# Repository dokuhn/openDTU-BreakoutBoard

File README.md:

# openDTU Breakout Board

 [![CC BY-NC-SA 4.0][cc-by-nc-sa-shield]][cc-by-nc-sa]

To read Hoymiles inverters there is a nice project called [OpenDTU](https://github.com/tbnobody/OpenDTU) which uses an ESP32 to talk to them. 

<br>

To extend this project with a hardware component this small KiCAD board was created. With it it should be possible for the not experienced in soldering person to build an own OpenDTU easier. But also the possibility to add further ideas, like temperature sensors, display etc.. In a second step it is also possible to design a board with all the necessary components on it directly. 

<br>

The first batch of 10 pieces is partially built and tested. Further tests will follow. Extensions of the board will be maintained in a second branch. 

## Donations

As you can see I am in the process of developing a SMT/SMD variant. To support the first 10-25 prototype boards you are welcome to make a donation. This donation should be used to compensate the material costs for components, boards and consumables (soldering paste, etc.). Through my membership in the [Linux User Group Saar e.V.](https://lugsaar.de/) you support more than just me, you also support our community in similar creative and technical projects in the open source and open hardware domain. 

-PayPal: 

## Renderings

## Development

As described in the previous section, extensions or development stages are maintained in a separate branch. This section is to show exemplarily where the current developments are. Currently a SMD/SMT variant of the board is designed (see picture with the first placement). The SMT will make the board much smaller of course, so it will fit into small cases. All needed components for operation will be on the board. 

### New Features:

- All components on just one board
- Stable voltage supply
- MicroSD slot with support for a small file system to store e.g. measurement series (CSV or JSON files)
- USB-C (now more common than microUSB)
- Option to connect a small (I2C) display

##  Hardware you need

### ESP32 board

In principle, the hardware recommended [here](https://github.com/tbnobody/OpenDTU) has been used in this project. Unfortunately there are many different variants, especially in the MCU boards, so that you must be very careful that your board is pin-compatible with the following figure. 

[figure source](https://i0.wp.com/www.teachmemicro.com/wp-content/uploads/2020/06/NodeMCU-32S-Pinout.jpg?ssl=1)

### Capacitor

As you can see in the graphics above, an electrolytic capacitor is placed between the two boards. This capacitor should be as close as possible to the NRF24L01+ radio board. The size of the capacity should not be larger than 100 uF, typically capacity like 10uF or 22uF are recommended. This also corresponds to the typical capacity in the AP1117 datasheets (keep in mind that the noboard capacity of the ESP32 board has to be added). The voltage stability has to be higher than 3.3V, so all common 5V, 6.3V, 6.5V, 10V, 25V or even 50V are more than enough. 

## Case

## License 

This work is licensed under a
[Creative Commons Attribution-NonCommercial-ShareAlike 4.0 International License][cc-by-nc-sa].

[![CC BY-NC-SA 4.0][cc-by-nc-sa-image]][cc-by-nc-sa]

[cc-by-nc-sa]: http://creativecommons.org/licenses/by-nc-sa/4.0/
[cc-by-nc-sa-image]: https://licensebuttons.net/l/by-nc-sa/4.0/88x31.png
[cc-by-nc-sa-shield]: https://img.shields.io/badge/License-CC%20BY--NC--SA%204.0-lightgrey.svg

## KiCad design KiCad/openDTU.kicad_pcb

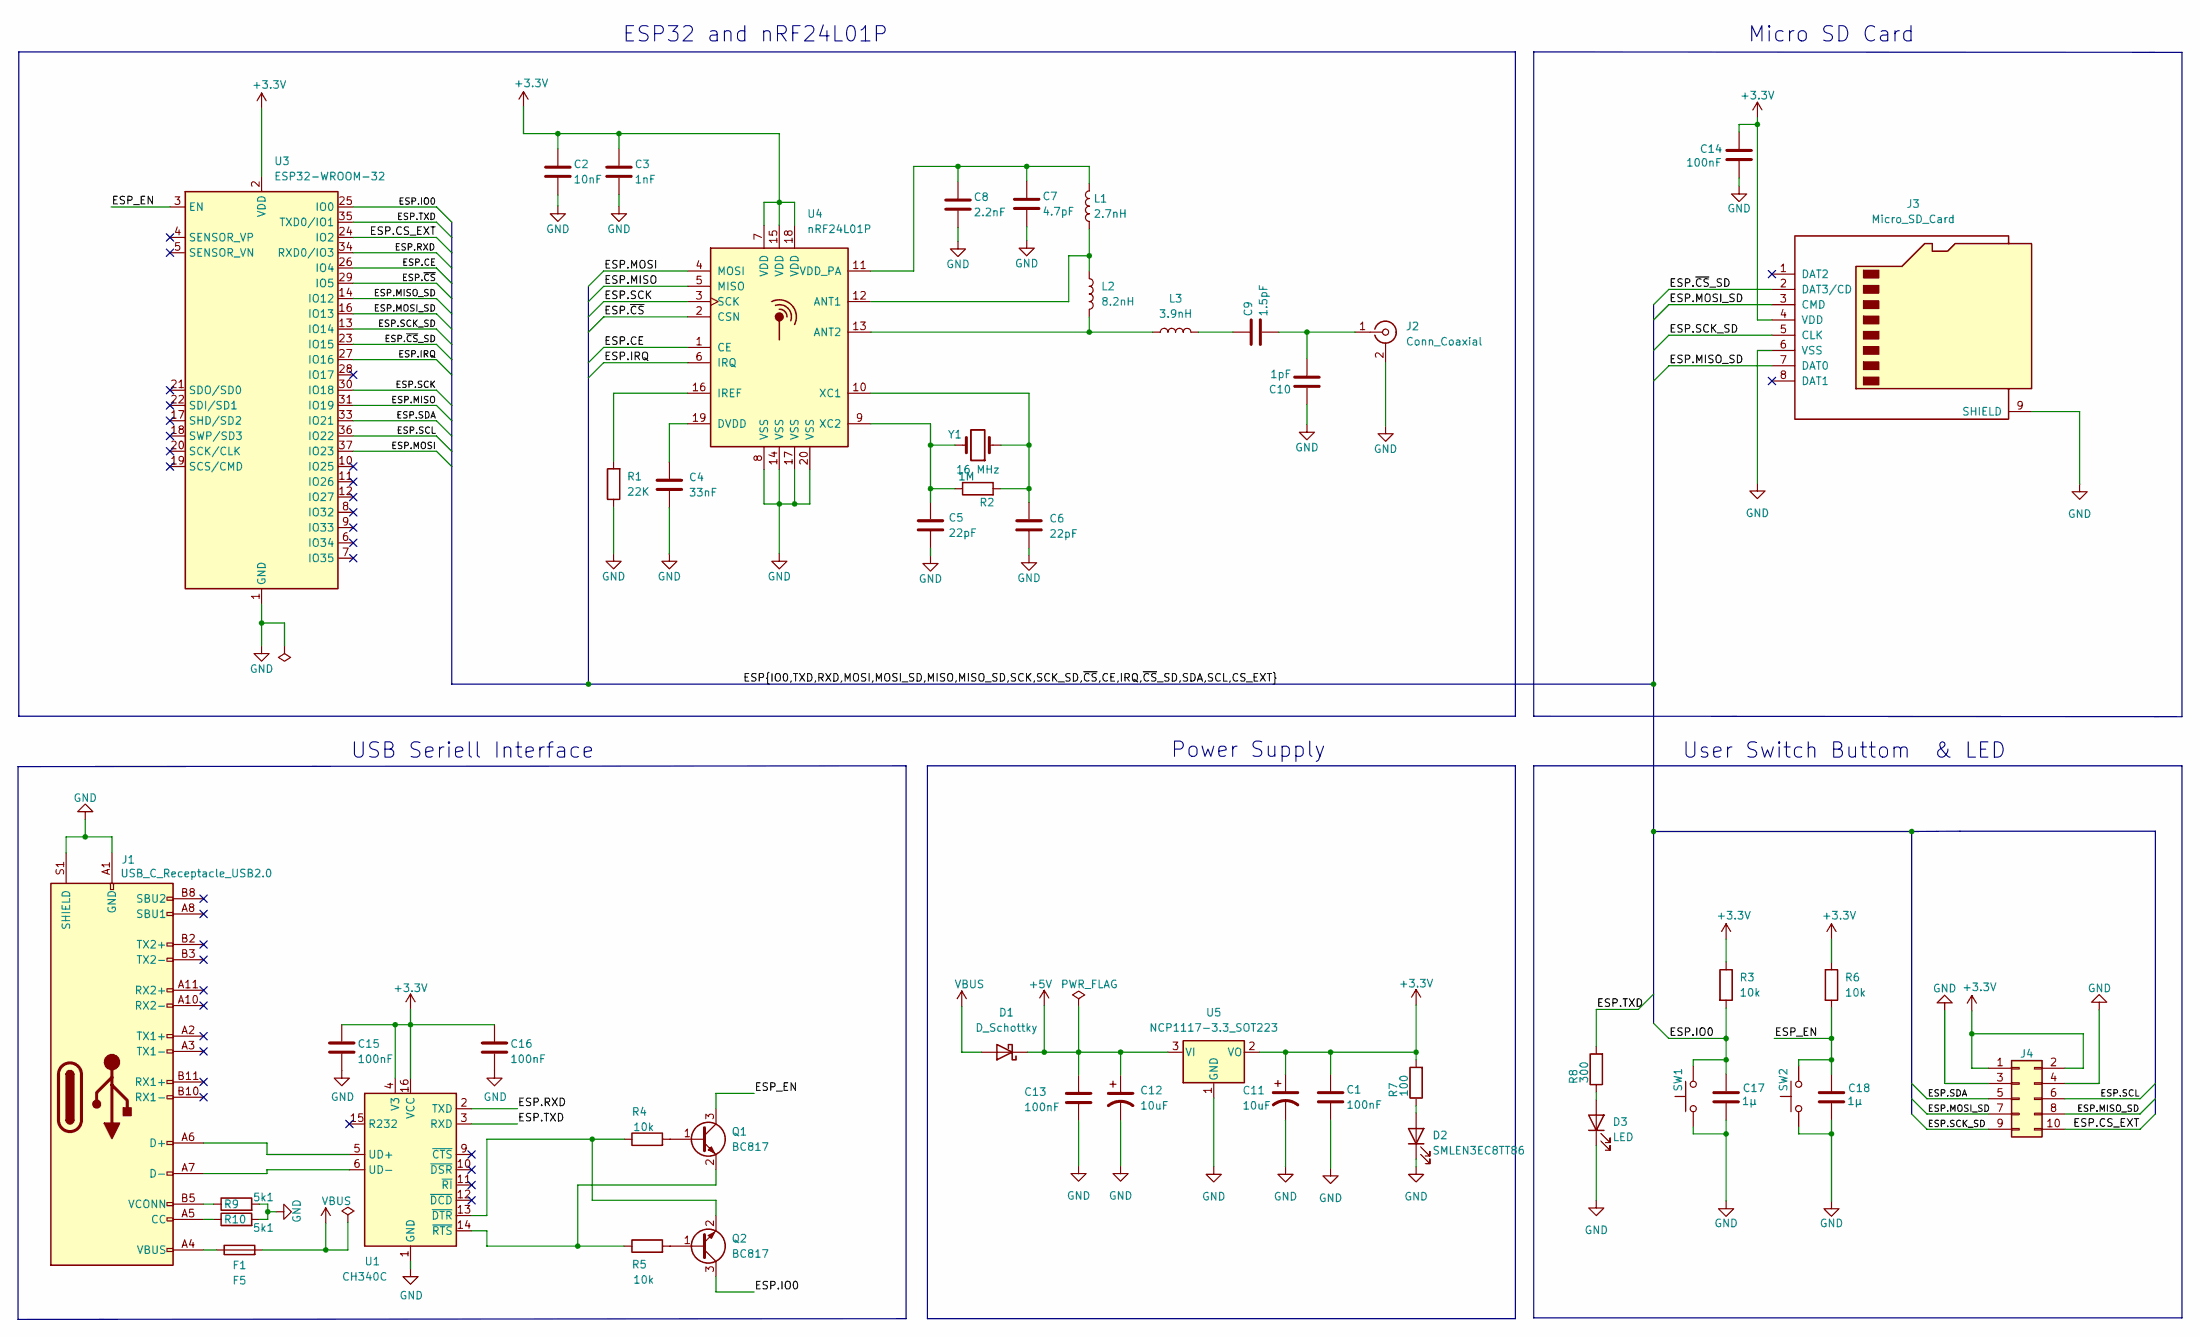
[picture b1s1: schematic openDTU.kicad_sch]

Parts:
C1, C13, C14: 100nF; C_0603_1608Metric_Pad1.08x0.95mm_HandSolder
C2: 10nF; C_0603_1608Metric_Pad1.08x0.95mm_HandSolder
C3: 1nF; C_0603_1608Metric_Pad1.08x0.95mm_HandSolder
C4: 33nF; C_0603_1608Metric_Pad1.08x0.95mm_HandSolder
C5, C6: 22pF; C_0603_1608Metric_Pad1.08x0.95mm_HandSolder
C7: 4.7pF; C_0603_1608Metric_Pad1.08x0.95mm_HandSolder
C8: 2.2nF; C_0603_1608Metric_Pad1.08x0.95mm_HandSolder
C9: 1.5pF; C_0603_1608Metric_Pad1.08x0.95mm_HandSolder
C10: 1pF; C_0603_1608Metric_Pad1.08x0.95mm_HandSolder
C11, C12: 10uF; C_1210_3225Metric_Pad1.33x2.70mm_HandSolder
C15, C16: 100nF; C_0603_1608Metric
C17, C18: 1µ; C_0603_1608Metric
D1: D_Schottky; D_1206_3216Metric
D2: SMLEN3EC8TT86; LED_0603_1608Metric_Pad1.05x0.95mm_HandSolder
D3: LED; LED_0603_1608Metric_Pad1.05x0.95mm_HandSolder
F1: F5; Fuse_Littelfuse-NANO2-451_453
J1: USB_C_Receptacle_USB2.0; USB_C_Receptacle_GCT_USB4105-xx-A_16P_TopMnt_Horizontal
J2: Conn_Coaxial; SMA_Molex_73251-2200_Horizontal
J3: Micro_SD_Card; microSD_HC_Hirose_DM3AT-SF-PEJM5
J4: Conn_02x05_Counter_Clockwise; PinHeader_2x05_P1.27mm_Vertical
L1: 2.7nH; L_0603_1608Metric_Pad1.05x0.95mm_HandSolder
L2: 8.2nH; L_0603_1608Metric_Pad1.05x0.95mm_HandSolder
L3: 3.9nH; L_0603_1608Metric_Pad1.05x0.95mm_HandSolder
Q1, Q2: BC817; SOT-23
R1: 22K; R_0603_1608Metric_Pad0.98x0.95mm_HandSolder
R2: 1M; R_0603_1608Metric_Pad0.98x0.95mm_HandSolder
R3, R6: 10k; R_0603_1608Metric_Pad0.98x0.95mm_HandSolder
R4, R5: 10k; R_0603_1608Metric
R7: 100; R_0603_1608Metric
R8: 300; R_0603_1608Metric
R9, R10: 5k1; R_0603_1608Metric
SW1, SW2: SW_Push; SW_SPST_B3U-1000P
U1: CH340C; SOIC-16_3.9x9.9mm_P1.27mm
U3: ESP32-WROOM-32
U4: nRF24L01P; QFN-20-1EP_4x4mm_P0.5mm_EP2.5x2.5mm
U5: NCP1117-3.3_SOT223; SOT-223-3_TabPin2
Y1: 16 MHz; Crystal_SMD_3225-4Pin_3.2x2.5mm

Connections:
+3.3V: C1.1, C2.1, C3.1, C11.1, C14.1, C15.1, C16.1, J3.4 (VDD), J4.1, J4.2, R3.1, R6.1, R7.2, U1.4 (V3), U1.16 (VCC), U3.2 (VDD), U4.7 (VDD), U4.15 (VDD), U4.18 (VDD), U5.2 (VO)
+5V: C12.1, C13.1, D1.1 (K), U5.3 (VI)
/ESP.CE: U3.26 (IO4), U4.1 (CE)
/ESP.CS_EXT: J4.10, U3.24 (IO2)
/ESP.IO0: C17.1, Q2.3 (C), R3.2, SW1.2, U3.25 (IO0)
/ESP.IRQ: U3.27 (IO16), U4.6 (IRQ)
/ESP.MISO: U3.31 (IO19), U4.5 (MISO)
/ESP.MISO_SD: J3.7 (DAT0), J4.8, U3.14 (IO12)
/ESP.MOSI: U3.37 (IO23), U4.4 (MOSI)
/ESP.MOSI_SD: J3.3 (CMD), J4.7, U3.16 (IO13)
/ESP.RXD: U1.2 (TXD), U3.34 (RXD0/IO3)
/ESP.SCK: U3.30 (IO18), U4.3 (SCK)
/ESP.SCK_SD: J3.5 (CLK), J4.9, U3.13 (IO14)
/ESP.SCL: J4.6, U3.36 (IO22)
/ESP.SDA: J4.5, U3.33 (IO21)
/ESP.TXD: R8.2, U1.3 (RXD), U3.35 (TXD0/IO1)
/ESP.~CS: U3.29 (IO5), U4.2 (CSN)
/ESP.~CS_SD: J3.2 (DAT3/CD), U3.23 (IO15)
/ESP_EN: C18.1, Q1.3 (C), R6.2, SW2.2, U3.3 (EN)
GND: C1.2, C2.2, C3.2, C4.2, C5.2, C6.2, C7.2, C8.2, C10.1, C11.2, C12.2, C13.2, C14.2, C15.2, C16.2, C17.2, C18.2, D2.1 (K), D3.1 (K), J1.A1 (GND), J1.A12 (GND), J1.B1 (GND), J1.B12 (GND), J1.S1 (SHIELD), J2.2 (Ext), J3.6 (VSS), J3.9 (SHIELD), J4.3, J4.4, R1.1, R9.2, R10.2, SW1.1, SW2.1, U1.1 (GND), U3.1 (GND), U3.15 (GND), U3.38 (GND), U3.39 (GND), U4.8 (VSS), U4.14 (VSS), U4.17 (VSS), U4.20 (VSS), U4.21, U5.1 (GND)
unnamed: C4.1, U4.19 (DVDD)
unnamed: C5.1, R2.1, U4.9 (XC2), Y1.3
unnamed: C6.1, R2.2, U4.10 (XC1), Y1.1
unnamed: C7.1, C8.1, L1.2, U4.11 (VDD_PA)
unnamed: C9.1, L3.2
unnamed: C9.2, C10.2, J2.1 (In)
unnamed: D2.2 (A), R7.1
unnamed: D3.2 (A), R8.1
unnamed: F1.1, J1.A4 (VBUS), J1.A9 (VBUS), J1.B4 (VBUS), J1.B9 (VBUS)
unnamed: J1.A5 (CC), R10.1
unnamed: J1.A6 (D+), J1.B6 (D+), U1.5 (UD+)
unnamed: J1.A7 (D-), J1.B7 (D-), U1.6 (UD-)
unnamed: J1.B5 (VCONN), R9.1
unnamed: L1.1, L2.1, U4.12 (ANT1)
unnamed: L2.2, L3.1, U4.13 (ANT2)
unnamed: Q1.1 (B), R4.2
unnamed: Q1.2 (E), R5.1, U1.14 (~RTS)
unnamed: Q2.1 (B), R5.2
unnamed: Q2.2 (E), R4.1, U1.13 (~DTR)
unnamed: R1.2, U4.16 (IREF)
VBUS: D1.2 (A), F1.2

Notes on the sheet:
Micro SD Card
USB Seriell Interface
User Switch Buttom & LED
ESP32 and nRF24L01P
Power Supply

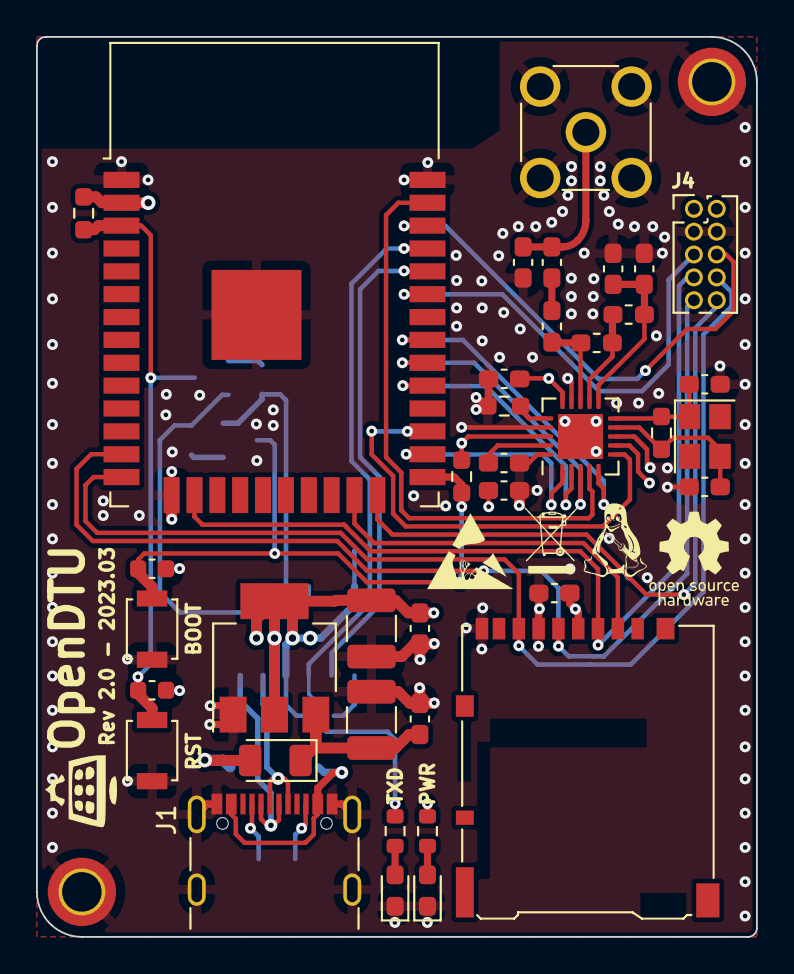
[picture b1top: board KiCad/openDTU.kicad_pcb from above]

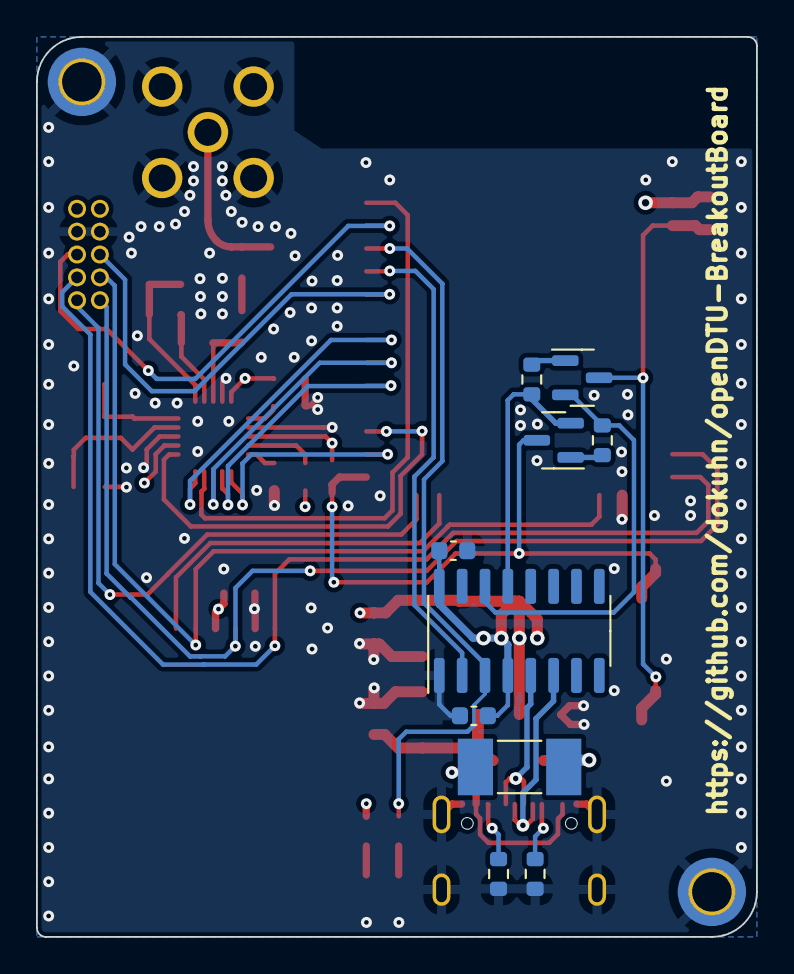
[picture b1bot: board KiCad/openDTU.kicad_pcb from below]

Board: 4 copper layers, 40.0 x 50.0 mm, 48 parts (10 on the bottom side), 41 nets.

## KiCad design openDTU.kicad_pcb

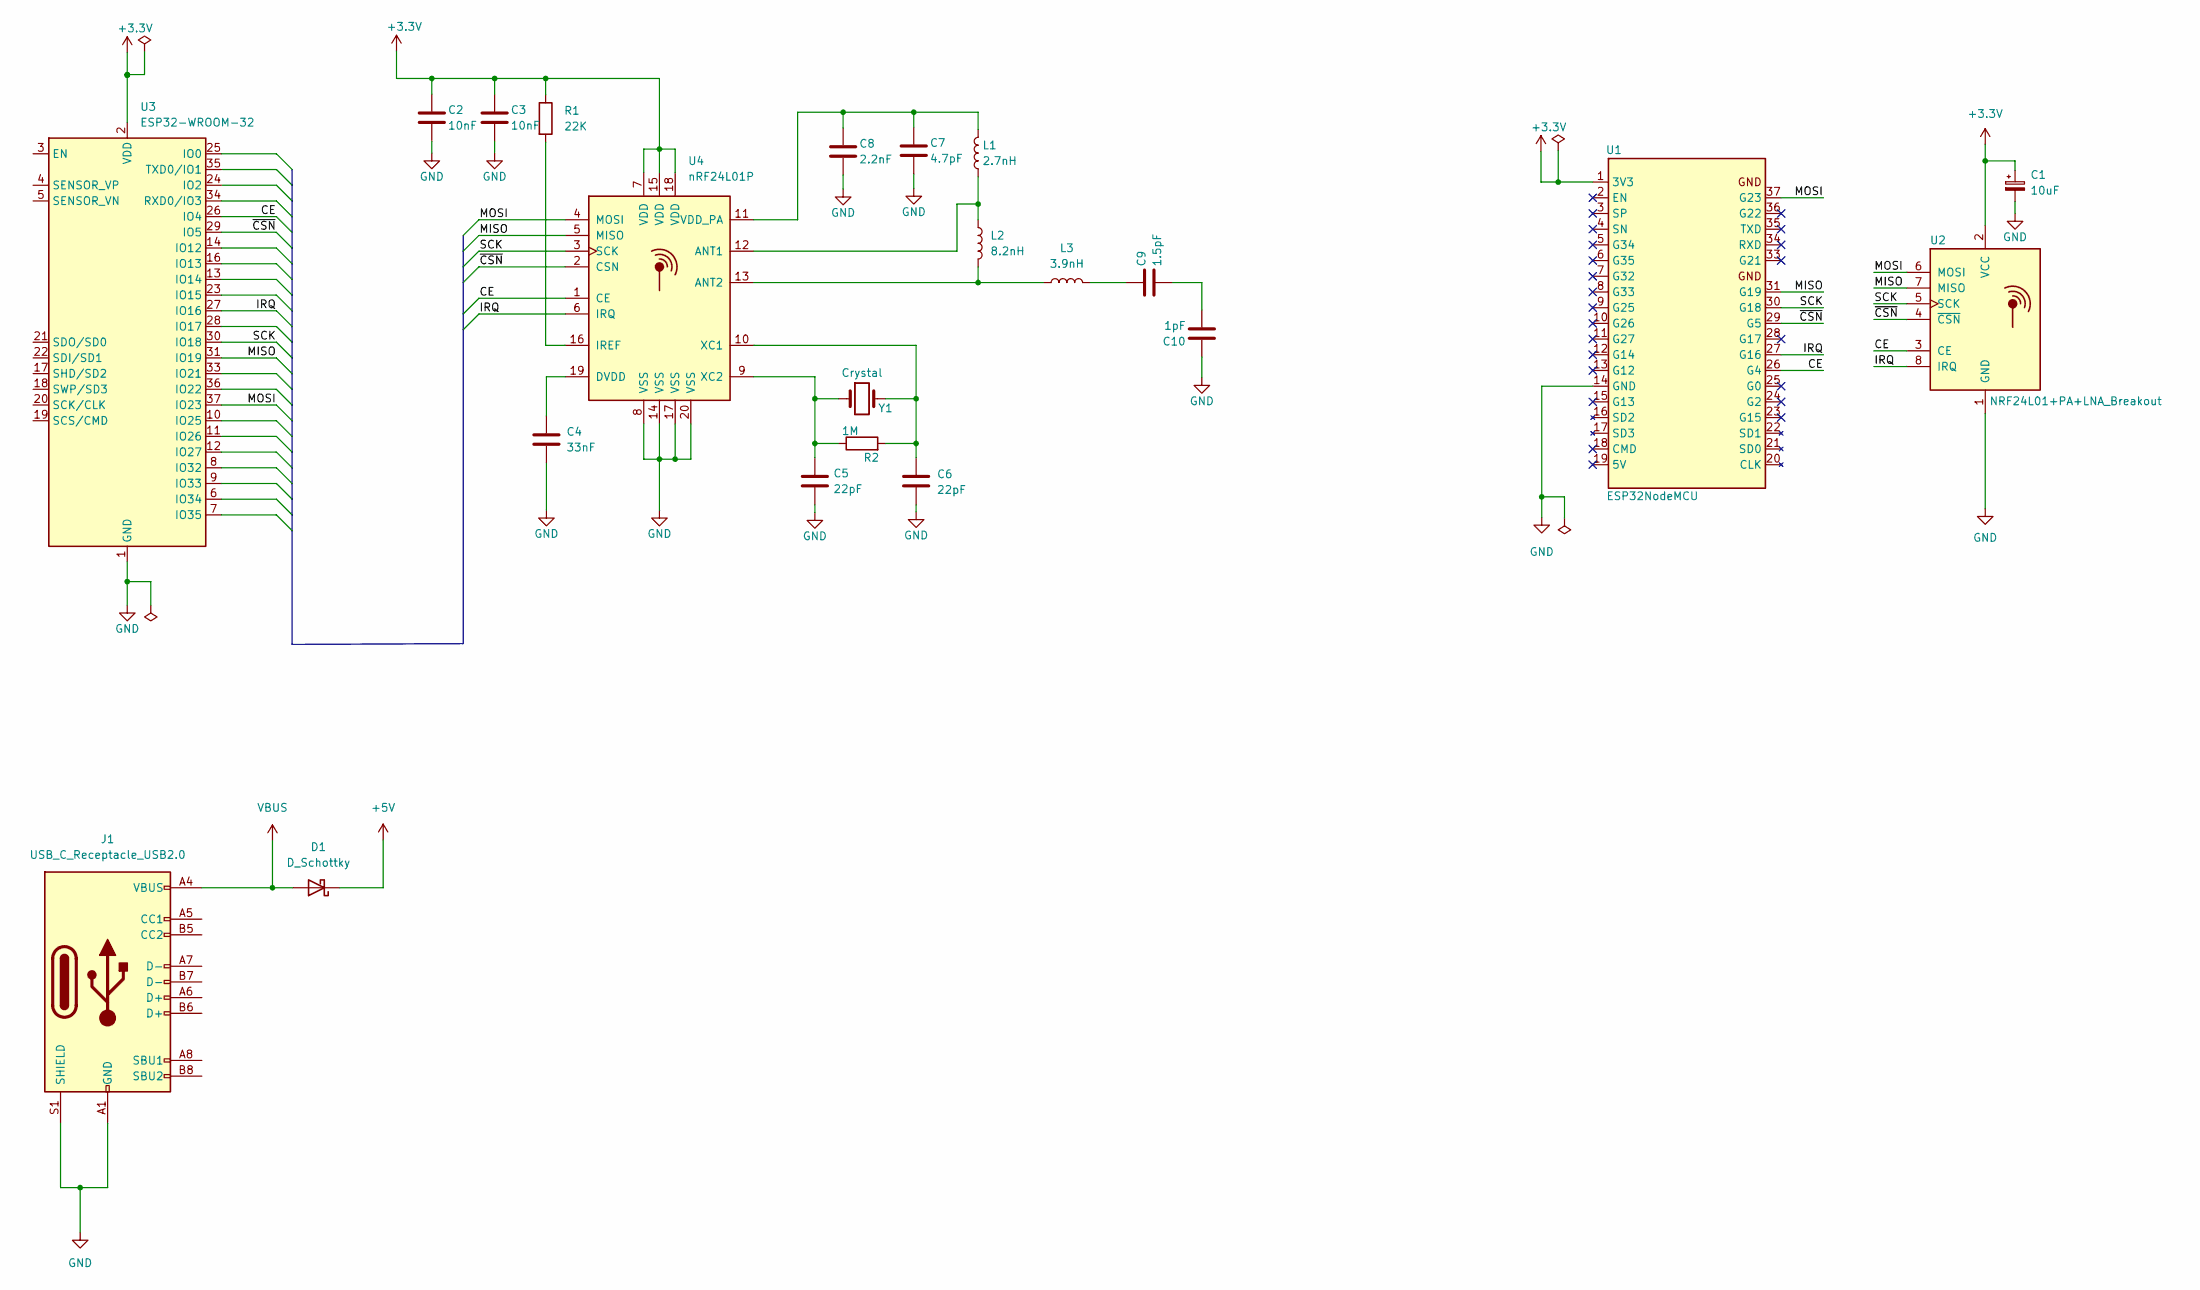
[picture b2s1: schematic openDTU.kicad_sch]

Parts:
C1: 10uF; CP_Radial_D5.0mm_P2.50mm
C2, C3: 10nF; C_0603_1608Metric_Pad1.08x0.95mm_HandSolder
C4: 33nF; C_0603_1608Metric_Pad1.08x0.95mm_HandSolder
C5, C6: 22pF; C_0603_1608Metric_Pad1.08x0.95mm_HandSolder
C7: 4.7pF; C_0603_1608Metric_Pad1.08x0.95mm_HandSolder
C8: 2.2nF; C_0603_1608Metric_Pad1.08x0.95mm_HandSolder
C9: 1.5pF; C_0603_1608Metric_Pad1.08x0.95mm_HandSolder
C10: 1pF; C_0603_1608Metric_Pad1.08x0.95mm_HandSolder
D1: D_Schottky; D_1206_3216Metric
J1: USB_C_Receptacle_USB2.0
L1: 2.7nH; L_0603_1608Metric_Pad1.05x0.95mm_HandSolder
L2: 8.2nH; L_0603_1608Metric_Pad1.05x0.95mm_HandSolder
L3: 3.9nH; L_0603_1608Metric_Pad1.05x0.95mm_HandSolder
R1: 22K; R_0603_1608Metric_Pad0.98x0.95mm_HandSolder
R2: 1M; R_0603_1608Metric_Pad0.98x0.95mm_HandSolder
U1: ESP32NodeMCU; ESP32-NodeMCU_WROOM_32
U2: NRF24L01+PA+LNA_Breakout; nRF24L01+PA+LNA_Breakout
U3: ESP32-WROOM-32
U4: nRF24L01P; QFN-20-1EP_4x4mm_P0.5mm_EP2.5x2.5mm
Y1: Crystal; Crystal_SMD_3225-4Pin_3.2x2.5mm

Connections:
+3.3V: C1.1, C2.1, C3.1, R1.1, U1.1 (3V3), U2.2 (VCC), U4.7 (VDD), U4.15 (VDD), U4.18 (VDD)
+5V: D1.1 (K)
/CE: U1.26 (G4), U2.3 (CE), U3.26 (IO4), U4.1 (CE)
/IRQ: U1.27 (G16), U2.8 (IRQ), U3.27 (IO16), U4.6 (IRQ)
/MISO: U1.31 (G19), U2.7 (MISO), U3.31 (IO19), U4.5 (MISO)
/MOSI: U1.37 (G23), U2.6 (MOSI), U3.37 (IO23), U4.4 (MOSI)
/SCK: U1.30 (G18), U2.5 (SCK), U3.30 (IO18), U4.3 (SCK)
/~CSN: U1.29 (G5), U2.4 (~CSN), U3.29 (IO5), U4.2 (CSN)
GND: C1.2, C2.2, C3.2, C4.2, C5.2, C6.2, C7.2, C8.2, C10.1, J1.A1 (GND), J1.A12 (GND), J1.B1 (GND), J1.B12 (GND), J1.S1 (SHIELD), U1.14 (GND), U1.32 (GND), U1.38 (GND), U2.1 (GND), U3.1 (GND), U3.15 (GND), U3.38 (GND), U3.39 (GND), U4.8 (VSS), U4.14 (VSS), U4.17 (VSS), U4.20 (VSS)
unnamed: C4.1, U4.19 (DVDD)
unnamed: C5.1, R2.1, U4.9 (XC2), Y1.1
unnamed: C6.1, R2.2, U4.10 (XC1), Y1.2
unnamed: C7.1, C8.1, L1.2, U4.11 (VDD_PA)
unnamed: C9.1, L3.2
unnamed: C9.2, C10.2
unnamed: L1.1, L2.1, U4.12 (ANT1)
unnamed: L2.2, L3.1, U4.13 (ANT2)
unnamed: R1.2, U4.16 (IREF)
VBUS: D1.2 (A), J1.A4 (VBUS), J1.A9 (VBUS), J1.B4 (VBUS), J1.B9 (VBUS)

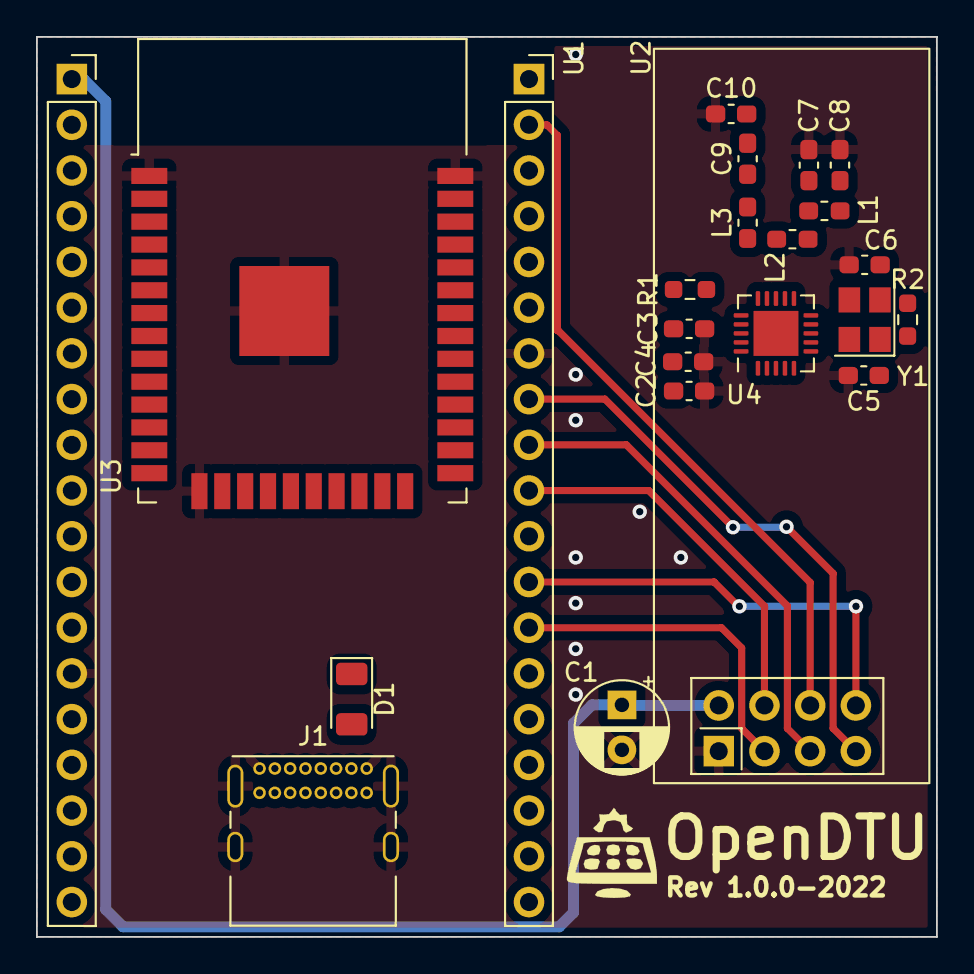
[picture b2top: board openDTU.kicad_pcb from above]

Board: 2 copper layers, 50.0 x 50.0 mm, 22 parts (0 on the bottom side), 18 nets.

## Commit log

2022-10-03 first init
2022-10-04 connecting nRF24L01+ to the ESP32 in schematic
2022-10-07 adding simple README.md file
2022-10-21 adding OpenDTU Logo and some informations on the silkscreen
2022-10-21 chanching track width and adding mountinghole to support the NRF34L01+ Board
2022-10-21 Adding some Testpads for signals between ESP32 and nRF24L01+. Adding vias to connect Bottom and Top GND Copper Zone.
2022-10-21 Adding Gerber files for the first Order
2022-11-13 adding adding picture and description of first batch
2022-11-20 change file structure
2022-11-27 adding LICENSE file
2022-11-28 adding Lisence section to README file
2022-11-28 fixing spelling eroor in README file
2022-11-30 adding first SMT parts to schematic and PCB, like MCU and nRF24L01+
2022-11-30 adding section in README file to descripe developments
2022-12-10 adding USB-C connector for power supply
2022-12-16 updating file structur
2022-12-17 Adding power supply IC and SMA connector.
2022-12-18 Add 3d Print Files für OpenDTU case
2022-12-18 adding 3D Model for USB-C connector
2022-12-18 updating develop rendering and adding case photos to README.md
2022-12-28 adding microSD socket and reset switch to schematic
2022-12-28 adding BOOT switch buttom
2023-01-06 adding User (GPIO1) and Power LED
2023-01-06 adding new development state
2023-01-13 adding some description of the recommended MCU board an capacitor
2023-01-14 adding donation section to README file
2023-01-14 update README file to set nice donate icon
2023-01-15 adding short list of new features in SMT variant
2023-01-15 reduce the board size and beautify the placement
2023-01-21 routing first parts
2023-01-29 adding pin header for I2C,SPI, etc.
2023-01-29 update README file to link image of development to branch
2023-02-03 changing USB-C connector and switching GND and +3V3 inner layer
2023-02-05 all tracks first time routed
2023-02-11 adding Frequency value to crystal an fixing crystal pin/footrpint assignment
2023-02-22 adding 5k1 resistor for A5 and B5 of usb-c
2023-02-22 update color of ESP32 wroom module
2023-03-05 first batch of smt variant ordered
2023-03-24 fixing bug with wrong voltage at USB-Seriell Interface IC
2023-03-30 exposed pad below the nRF24L01p added to GND net
